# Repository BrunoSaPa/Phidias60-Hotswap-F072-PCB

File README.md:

Hotswap PCB for 60% mechanical keyboard, with daughterboard support, using Gondolindrim's Reset circtuit for the SMTF072 from https://acheronproject.com/alexandria/alexandria/

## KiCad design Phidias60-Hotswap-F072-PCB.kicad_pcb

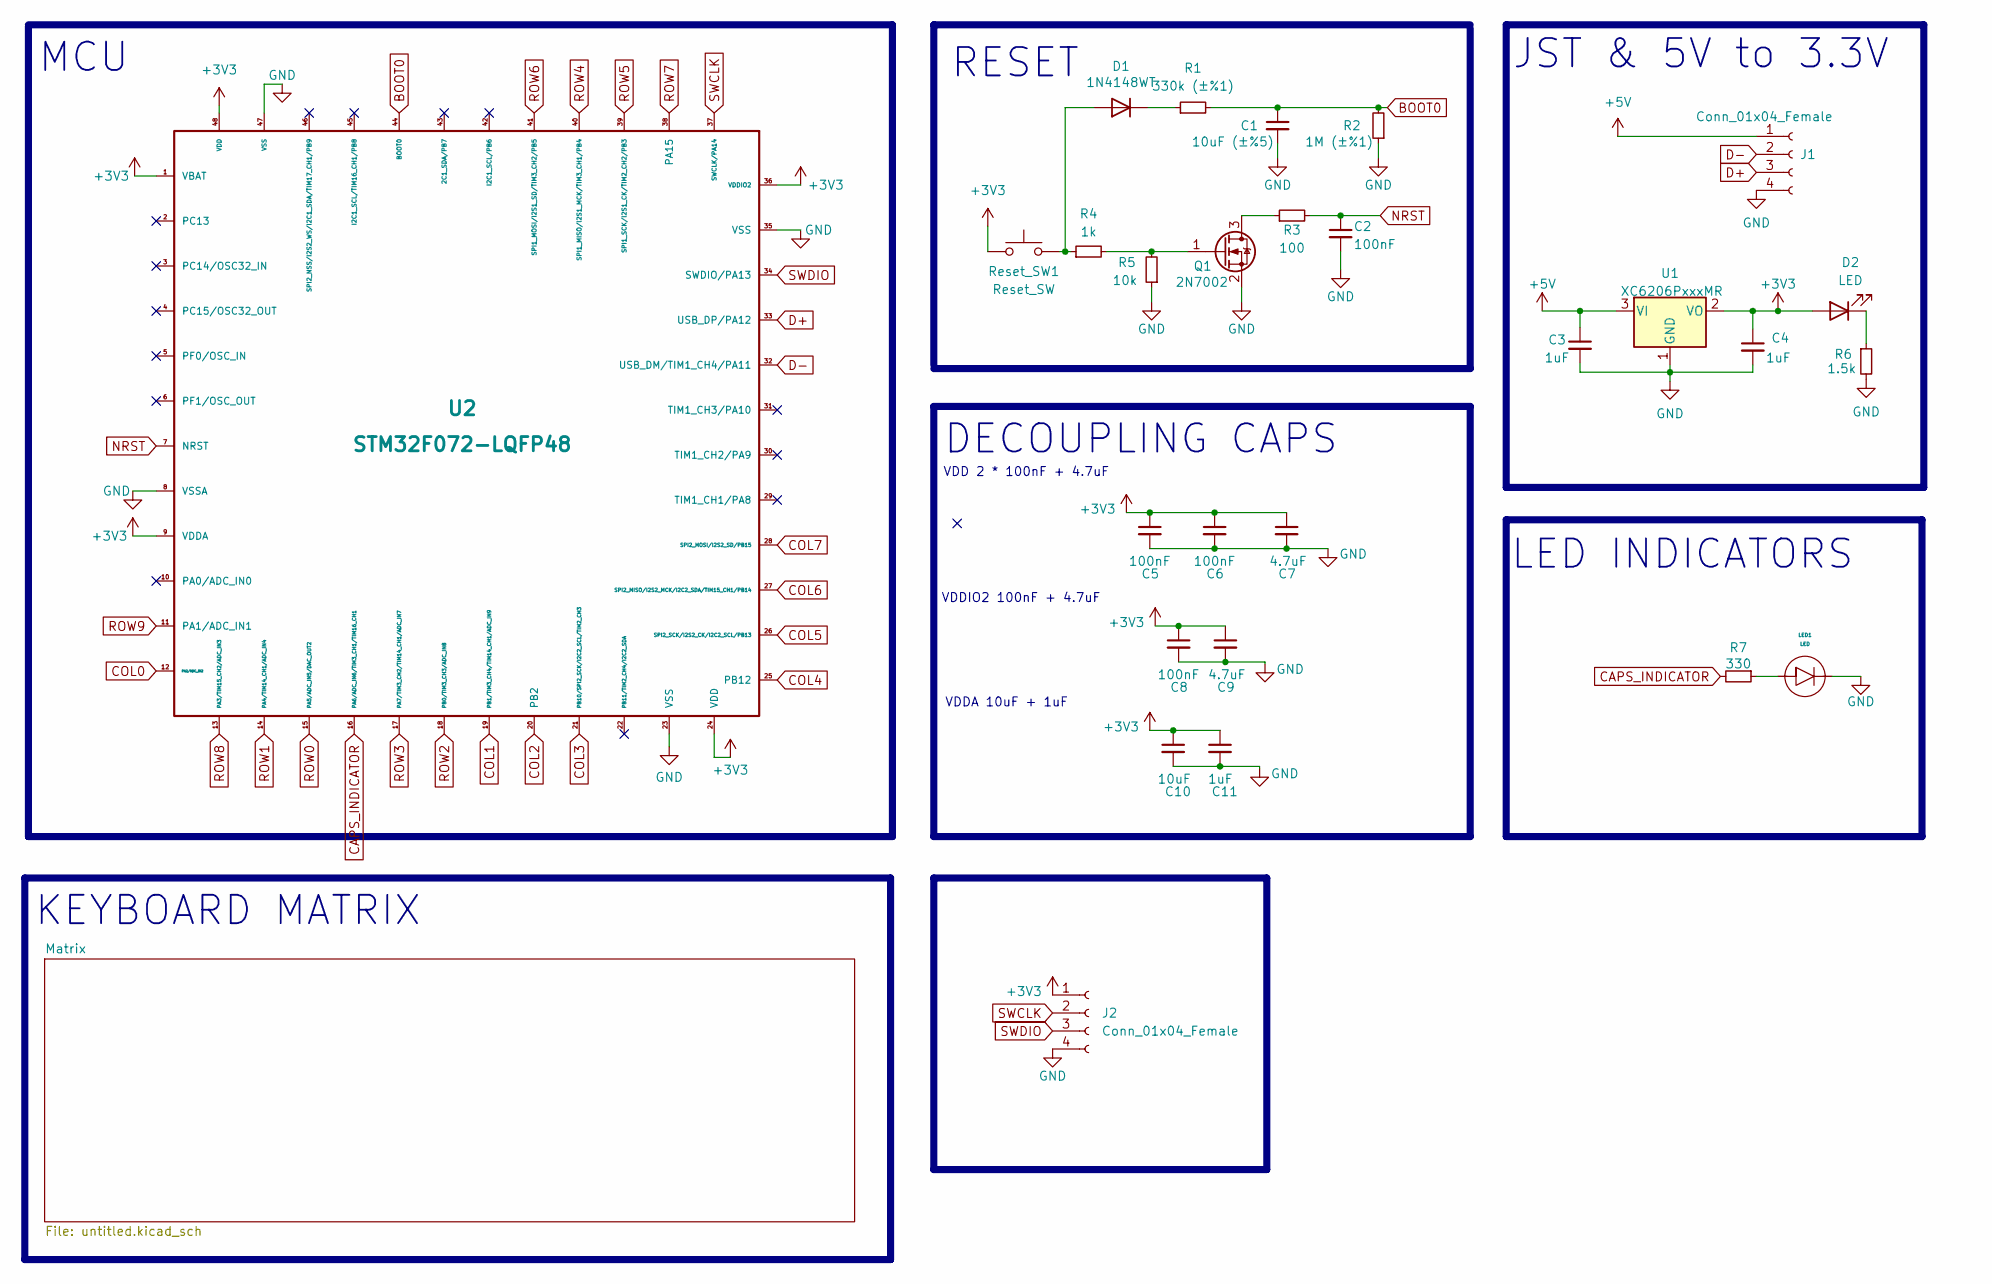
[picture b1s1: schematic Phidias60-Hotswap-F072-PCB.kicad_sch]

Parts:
C1: 10uF (±%5); C_0805_2012Metric
C2, C5, C6, C8: 100nF; C_0805_2012Metric
C3, C4, C11: 1uF; C_0805_2012Metric
C7, C9: 4.7uF; C_0805_2012Metric
C10: 10uF; C_0805_2012Metric
D1: 1N4148WT; D_SOD-523
D2: LED; LED_0805_2012Metric
J1: Conn_01x04_Female; SM04B-SRSS-TB(LF)(SN)
J2: Conn_01x04_Female; PinHeader_1x4_P2.54mm_Vertical
LED1: LED; LED_THT_2.54mm
Q1: 2N7002; SOT-23
R1: 330k (±%1); R_0603_1608Metric_Pad0.98x0.95mm_HandSolder
R2: 1M (±%1); R_0603_1608Metric_Pad0.98x0.95mm_HandSolder
R3: 100; R_0603_1608Metric_Pad0.98x0.95mm_HandSolder
R4: 1k; R_0603_1608Metric_Pad0.98x0.95mm_HandSolder
R5: 10k; R_0603_1608Metric_Pad0.98x0.95mm_HandSolder
R6: 1.5k; R_0603_1608Metric_Pad0.98x0.95mm_HandSolder
R7: 330; R_0603_1608Metric_Pad0.98x0.95mm_HandSolder
Reset_SW1: Reset_SW; SW_SPST_SKQG_WithStem
U1: XC6206PxxxMR; SOT-23
U2: STM32F072-LQFP48; LQFP-48_7x7mm_P0.5mm

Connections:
+3V3: C4.1, C5.1, C6.1, C7.1, C8.1, C9.1, C10.1, C11.1, D2.2 (A), J2.1, Reset_SW1.1, U1.2 (VO), U2.1 (VBAT), U2.9 (VDDA), U2.24 (VDD), U2.36 (VDDIO2), U2.48 (VDD)
+5V: C3.1, J1.1, U1.3 (VI)
BOOT0: C1.1, R1.2, R2.2, U2.44 (BOOT0)
CAPS_INDICATOR: R7.2, U2.16 (PA6/ADC_IN6/TIM3_CH1/TIM16_CH1)
COL0: U2.12 (PA2/ADC_IN2); also elsewhere on the board
COL1: U2.19 (PB1/TIM3_CH4/TIM14_CH1/ADC_IN9); also elsewhere on the board
COL2: U2.20 (PB2); also elsewhere on the board
COL3: U2.21 (PB10/SPI2_SCK/I2C2_SCL/TIM2_CH3); also elsewhere on the board
COL4: U2.25 (PB12); also elsewhere on the board
COL5: U2.26 (SPI2_SCK/I2S2_CK/I2C2_SCL/PB13); also elsewhere on the board
COL6: U2.27 (SPI2_MISO/I2S2_MCK/I2C2_SDA/TIM15_CH1/P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); also elsewhere on the board
COL7: U2.28 (SPI2_MOSI/I2S2_SD/PB15); also elsewhere on the board
D+: J1.3, U2.33 (USB_DP/PA12)
D-: J1.2, U2.32 (USB_DM/TIM1_CH4/PA11)
GND: C1.2, C2.2, C3.2, C4.2, C5.2, C6.2, C7.2, C8.2, C9.2, C10.2, C11.2, J1.4, J2.4, LED1.K, Q1.2 (S), R2.1, R5.1, R6.2, U1.1 (GND), U2.8 (VSSA), U2.23 (VSS), U2.35 (VSS), U2.47 (VSS)
NRST: C2.1, R3.2, U2.7 (NRST)
unnamed: D1.2 (A), R4.1, Reset_SW1.2
unnamed: D1.1 (K), R1.1
unnamed: D2.1 (K), R6.1
unnamed: LED1.A, R7.1
unnamed: Q1.3 (D), R3.1
unnamed: Q1.1 (G), R4.2, R5.2
ROW0: U2.15 (PA5/ADC_IN5/DAC_OUT2); also elsewhere on the board
ROW1: U2.14 (PA4/TIM14_CH1/ADC_IN4); also elsewhere on the board
ROW2: U2.18 (PB0/TIM3_CH3/ADC_IN8); also elsewhere on the board
ROW3: U2.17 (PA7/TIM3_CH2/TIM14_CH1/ADC_IN7); also elsewhere on the board
ROW4: U2.40 (SPI1_MISO/I2S1_MCK/TIM3_CH1/PB4); also elsewhere on the board
ROW5: U2.39 (SPI1_SCK/I2S1_CK/TIM2_CH2/PB3); also elsewhere on the board
ROW6: U2.41 (SPI1_MOSI/I2S1_SD/TIM3_CH2/PB5); also elsewhere on the board
ROW7: U2.38 (PA15); also elsewhere on the board
ROW8: U2.13 (PA3/TIM15_CH2/ADC_IN3); also elsewhere on the board
ROW9: U2.11 (PA1/ADC_IN1); also elsewhere on the board
SWCLK: J2.2, U2.37 (SWCLK/PA14)
SWDIO: J2.3, U2.34 (SWDIO/PA13)

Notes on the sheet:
MCU
KEYBOARD MATRIX
VDD 2 * 100nF + 4.7uF
VDDIO2 100nF + 4.7uF
DECOUPLING CAPS
JST & 5V to 3.3V
LED INDICATORS
VDDA 10uF + 1uF
RESET

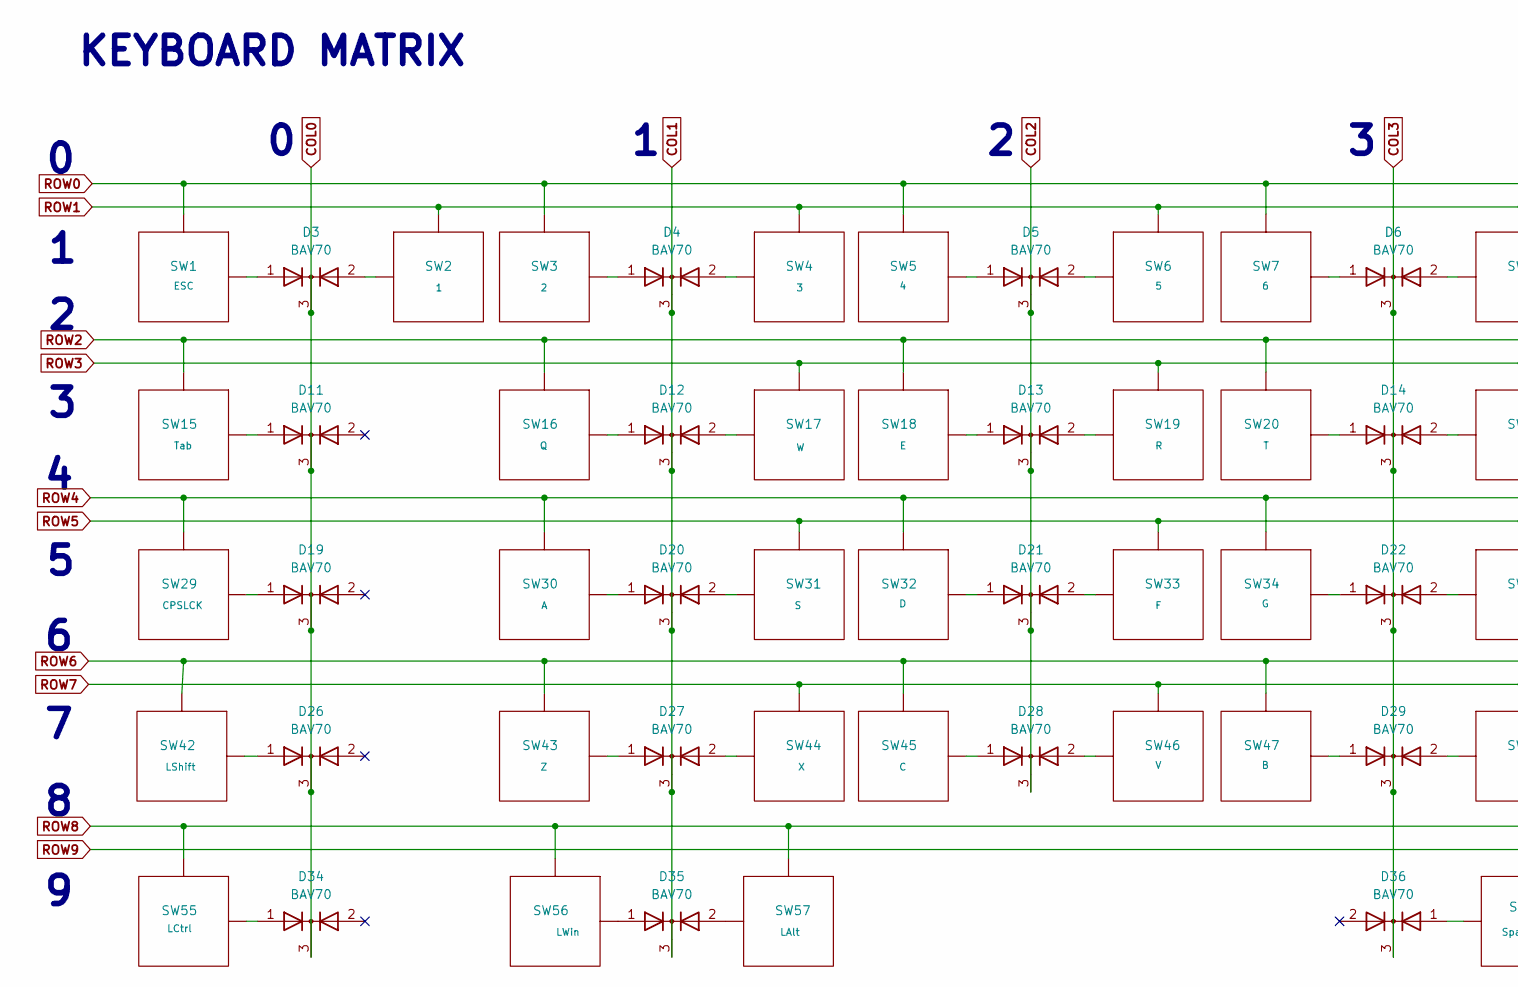
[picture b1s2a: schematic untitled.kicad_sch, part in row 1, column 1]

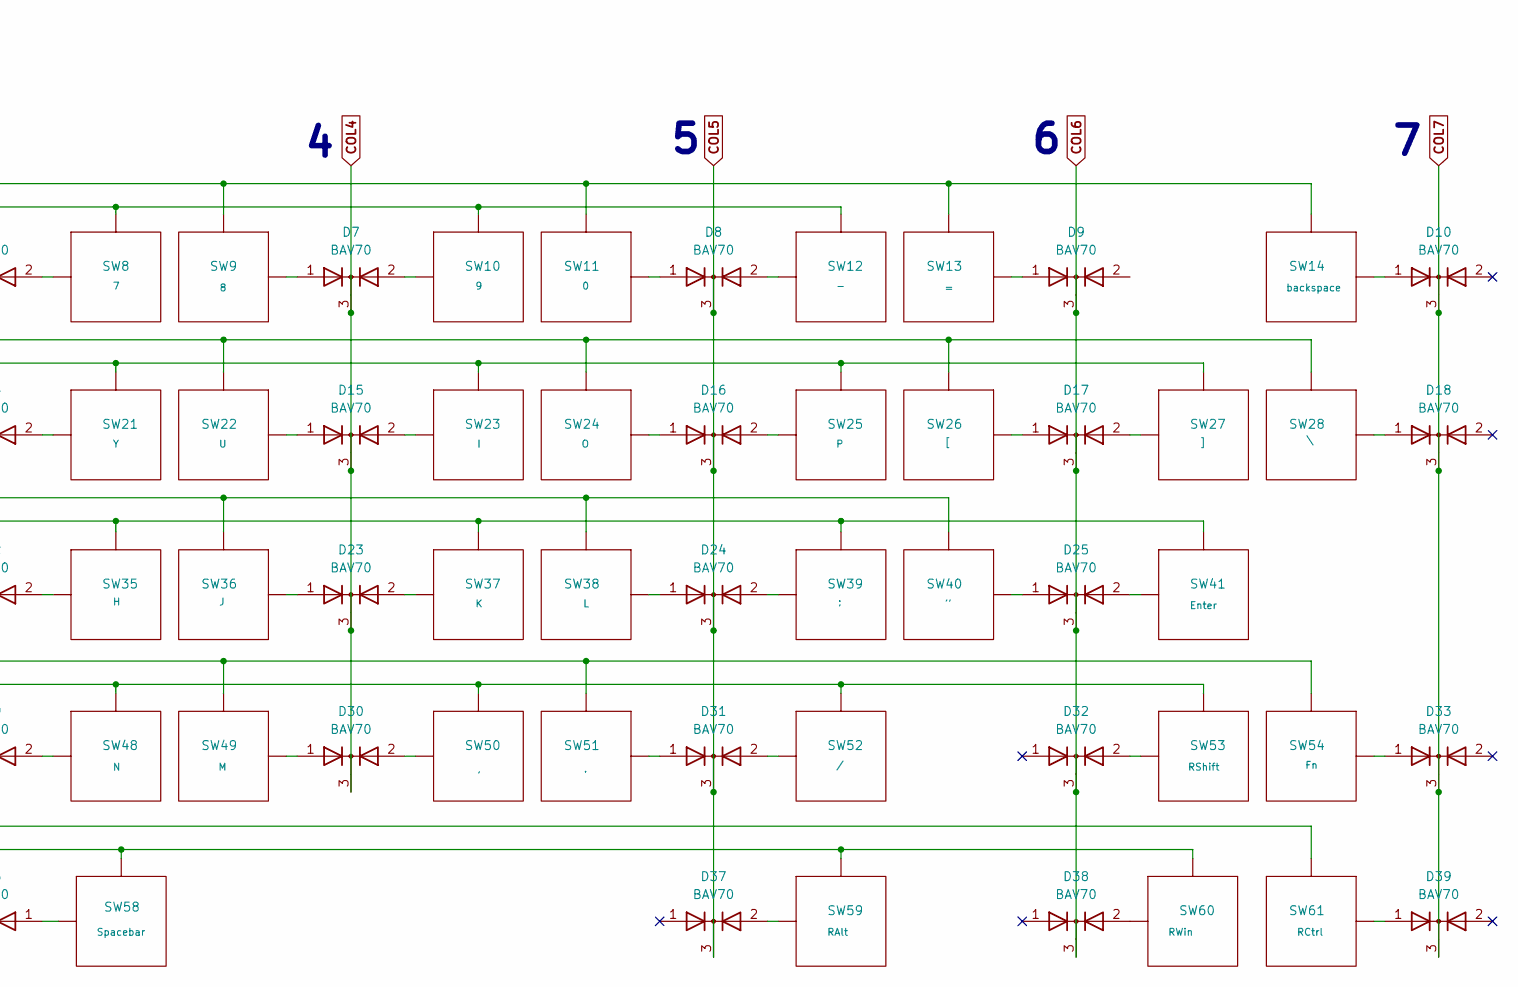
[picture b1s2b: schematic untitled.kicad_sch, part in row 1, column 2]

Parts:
D3, D4, D5, D6, D7, D8, D9, D10, D11, D12, D13, D14, D15, D16, D17, D18, D19, D20, D21, D22, D23, D24, D25, D26, D27, D28, D29, D30, D31, D32, D33, D34, D35, D36, D37, D38, D39: BAV70; SOT-23
SW1: ESC; MX-Hotswap-1U
SW2: 1; MX-Hotswap-1U
SW3: 2; MX-Hotswap-1U
SW4: 3; MX-Hotswap-1U
SW5: 4; MX-Hotswap-1U
SW6: 5; MX-Hotswap-1U
SW7: 6; MX-Hotswap-1U
SW8: 7; MX-Hotswap-1U
SW9: 8; MX-Hotswap-1U
SW10: 9; MX-Hotswap-1U
SW11: 0; MX-Hotswap-1U
SW12: -; MX-Hotswap-1U
SW13: =; MX-Hotswap-1U
SW14: backspace; MX-Hotswap-2U
SW15: Tab; MX-Hotswap-1.5U
SW16: Q; MX-Hotswap-1U
SW17: W; MX-Hotswap-1U
SW18: E; MX-Hotswap-1U
SW19: R; MX-Hotswap-1U
SW20: T; MX-Hotswap-1U
SW21: Y; MX-Hotswap-1U
SW22: U; MX-Hotswap-1U
SW23: I; MX-Hotswap-1U
SW24: O; MX-Hotswap-1U
SW25: P; MX-Hotswap-1U
SW26: [; MX-Hotswap-1U
SW27: ]; MX-Hotswap-1U
SW28: \; MX-Hotswap-1.5U
SW29: CPSLCK; MX-Hotswap-1.25U
SW30: A; MX-Hotswap-1U
SW31: S; MX-Hotswap-1U
SW32: D; MX-Hotswap-1U
SW33: F; MX-Hotswap-1U
SW34: G; MX-Hotswap-1U
SW35: H; MX-Hotswap-1U
SW36: J; MX-Hotswap-1U
SW37: K; MX-Hotswap-1U
SW38: L; MX-Hotswap-1U
SW39: ;; MX-Hotswap-1U
SW40: ''; MX-Hotswap-1U
SW41: Enter; MX-Hotswap-2.25U
SW42: LShift; MX-Hotswap-2.25U
SW43: Z; MX-Hotswap-1U
SW44: X; MX-Hotswap-1U
SW45: C; MX-Hotswap-1U
SW46: V; MX-Hotswap-1U
SW47: B; MX-Hotswap-1U
SW48: N; MX-Hotswap-1U
SW49: M; MX-Hotswap-1U
SW50: ,; MX-Hotswap-1U
SW51: .; MX-Hotswap-1U
SW52: /; MX-Hotswap-1U
SW53: RShift; MX-Hotswap-1.75U
SW54: Fn; MX-Hotswap-1U
SW55: LCtrl; MX-Hotswap-1.5U
SW56: LWin; MX-Hotswap-1U
SW57: LAlt; MX-Hotswap-1.5U
SW58: Spacebar; MX-Hotswap-7U-ReversedStabilizers
SW59: RAlt; MX-Hotswap-1.5U
SW60: RWin; MX-Hotswap-1U
SW61: RCtrl; MX-Hotswap-1.5U

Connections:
COL0: D3.3 (K), D11.3 (K), D19.3 (K), D26.3 (K), D34.3 (K); also elsewhere on the board
COL1: D4.3 (K), D12.3 (K), D20.3 (K), D27.3 (K), D35.3 (K); also elsewhere on the board
COL2: D5.3 (K), D13.3 (K), D21.3 (K), D28.3 (K); also elsewhere on the board
COL3: D6.3 (K), D14.3 (K), D22.3 (K), D29.3 (K), D36.3 (K); also elsewhere on the board
COL4: D7.3 (K), D15.3 (K), D23.3 (K), D30.3 (K); also elsewhere on the board
COL5: D8.3 (K), D16.3 (K), D24.3 (K), D31.3 (K), D37.3 (K); also elsewhere on the board
COL6: D9.3 (K), D17.3 (K), D25.3 (K), D32.3 (K), D38.3 (K); also elsewhere on the board
COL7: D10.3 (K), D18.3 (K), D33.3 (K), D39.3 (K); also elsewhere on the board
unnamed: D3.1 (A), SW1.1 (Col)
unnamed: D3.2 (A), SW2.1 (Col)
unnamed: D4.1 (A), SW3.1 (Col)
unnamed: D4.2 (A), SW4.1 (Col)
unnamed: D5.1 (A), SW5.1 (Col)
unnamed: D5.2 (A), SW6.1 (Col)
unnamed: D6.1 (A), SW7.1 (Col)
unnamed: D6.2 (A), SW8.1 (Col)
unnamed: D7.1 (A), SW9.1 (Col)
unnamed: D7.2 (A), SW10.1 (Col)
unnamed: D8.1 (A), SW11.1 (Col)
unnamed: D8.2 (A), SW12.1 (Col)
unnamed: D9.1 (A), SW13.1 (Col)
unnamed: D10.1 (A), SW14.1 (Col)
unnamed: D11.1 (A), SW15.1 (Col)
unnamed: D12.1 (A), SW16.1 (Col)
unnamed: D12.2 (A), SW17.1 (Col)
unnamed: D13.1 (A), SW18.1 (Col)
unnamed: D13.2 (A), SW19.1 (Col)
unnamed: D14.1 (A), SW20.1 (Col)
unnamed: D14.2 (A), SW21.1 (Col)
unnamed: D15.1 (A), SW22.1 (Col)
unnamed: D15.2 (A), SW23.1 (Col)
unnamed: D16.1 (A), SW24.1 (Col)
unnamed: D16.2 (A), SW25.1 (Col)
unnamed: D17.1 (A), SW26.1 (Col)
unnamed: D17.2 (A), SW27.1 (Col)
unnamed: D18.1 (A), SW28.1 (Col)
unnamed: D19.1 (A), SW29.1 (Col)
unnamed: D20.1 (A), SW30.1 (Col)
unnamed: D20.2 (A), SW31.1 (Col)
unnamed: D21.1 (A), SW32.1 (Col)
unnamed: D21.2 (A), SW33.1 (Col)
unnamed: D22.1 (A), SW34.1 (Col)
unnamed: D22.2 (A), SW35.1 (Col)
unnamed: D23.1 (A), SW36.1 (Col)
unnamed: D23.2 (A), SW37.1 (Col)
unnamed: D24.1 (A), SW38.1 (Col)
unnamed: D24.2 (A), SW39.1 (Col)
unnamed: D25.1 (A), SW40.1 (Col)
unnamed: D25.2 (A), SW41.1 (Col)
unnamed: D26.1 (A), SW42.1 (Col)
unnamed: D27.1 (A), SW43.1 (Col)
unnamed: D27.2 (A), SW44.1 (Col)
unnamed: D28.1 (A), SW45.1 (Col)
unnamed: D28.2 (A), SW46.1 (Col)
unnamed: D29.1 (A), SW47.1 (Col)
unnamed: D29.2 (A), SW48.1 (Col)
unnamed: D30.1 (A), SW49.1 (Col)
unnamed: D30.2 (A), SW50.1 (Col)
unnamed: D31.1 (A), SW51.1 (Col)
unnamed: D31.2 (A), SW52.1 (Col)
unnamed: D32.2 (A), SW53.1 (Col)
unnamed: D33.1 (A), SW54.1 (Col)
unnamed: D34.1 (A), SW55.1 (Col)
unnamed: D35.1 (A), SW56.1 (Col)
unnamed: D35.2 (A), SW57.1 (Col)
unnamed: D36.1 (A), SW58.1 (Col)
unnamed: D37.2 (A), SW59.1 (Col)
unnamed: D38.2 (A), SW60.1 (Col)
unnamed: D39.1 (A), SW61.1 (Col)
ROW0: SW1.2 (Row), SW3.2 (Row), SW5.2 (Row), SW7.2 (Row), SW9.2 (Row), SW11.2 (Row), SW13.2 (Row), SW14.2 (Row); also elsewhere on the board
ROW1: SW2.2 (Row), SW4.2 (Row), SW6.2 (Row), SW8.2 (Row), SW10.2 (Row), SW12.2 (Row); also elsewhere on the board
ROW2: SW15.2 (Row), SW16.2 (Row), SW18.2 (Row), SW20.2 (Row), SW22.2 (Row), SW24.2 (Row), SW26.2 (Row), SW28.2 (Row); also elsewhere on the board
ROW3: SW17.2 (Row), SW19.2 (Row), SW21.2 (Row), SW23.2 (Row), SW25.2 (Row), SW27.2 (Row); also elsewhere on the board
ROW4: SW29.2 (Row), SW30.2 (Row), SW32.2 (Row), SW34.2 (Row), SW36.2 (Row), SW38.2 (Row), SW40.2 (Row); also elsewhere on the board
ROW5: SW31.2 (Row), SW33.2 (Row), SW35.2 (Row), SW37.2 (Row), SW39.2 (Row), SW41.2 (Row); also elsewhere on the board
ROW6: SW42.2 (Row), SW43.2 (Row), SW45.2 (Row), SW47.2 (Row), SW49.2 (Row), SW51.2 (Row), SW54.2 (Row); also elsewhere on the board
ROW7: SW44.2 (Row), SW46.2 (Row), SW48.2 (Row), SW50.2 (Row), SW52.2 (Row), SW53.2 (Row); also elsewhere on the board
ROW8: SW55.2 (Row), SW56.2 (Row), SW57.2 (Row), SW61.2 (Row); also elsewhere on the board
ROW9: SW58.2 (Row), SW59.2 (Row), SW60.2 (Row); also elsewhere on the board

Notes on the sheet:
KEYBOARD MATRIX

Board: 2 copper layers, 125 parts (125 on the bottom side), 95 nets, no tracks yet.

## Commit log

2024-11-17 Unconnected pcb
